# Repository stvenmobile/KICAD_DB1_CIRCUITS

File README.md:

# KICAD_DB1

This repository contains KICAD materials related to circuit boards used in the DB1 robot.

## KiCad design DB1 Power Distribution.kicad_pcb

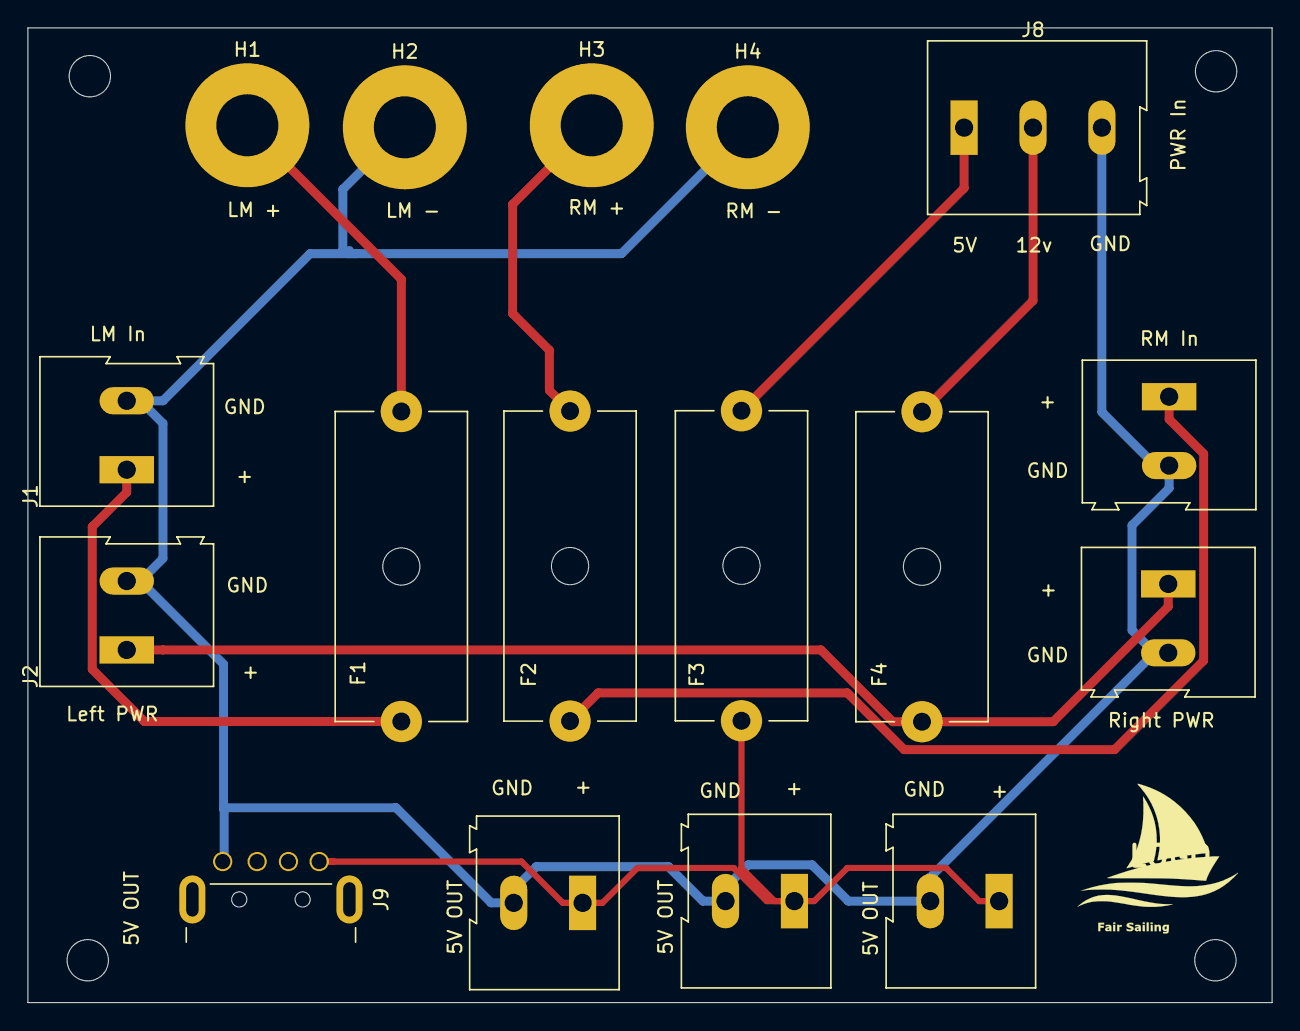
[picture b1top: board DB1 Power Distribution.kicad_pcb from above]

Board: 2 copper layers, 90.3 x 70.7 mm, 17 parts (0 on the bottom side), 9 nets.

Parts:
F1, F2, F3, F4: Fuse; Fuseholder_Cylinder-5x20mm_Schurter_0031_8201_Horizontal_Op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
H1: LM +; MountingHole_4.5mm_Pad
H2: LM -; MountingHole_4.5mm_Pad
H3: RM +; MountingHole_4.5mm_Pad
H4: RM -; MountingHole_4.5mm_Pad
J1: LM In; TerminalBlock_Altech_AK300-2_P5.00mm
J2: Left PWR; TerminalBlock_Altech_AK300-2_P5.00mm
J3: RM In; TerminalBlock_Altech_AK300-2_P5.00mm
J4: Right PWR; TerminalBlock_Altech_AK300-2_P5.00mm
J5, J6, J7: 5V Out; TerminalBlock_Altech_AK300-2_P5.00mm
J8: PWR In; TerminalBlock_Altech_AK300-3_P5.00mm
J9: USB_A; USB_A_CNCTech_1001-011-01101_Horizontal

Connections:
/5v: F3.2, J5.1, J6.1, J7.1, J9.1
/12v: F4.2, J2.1, J4.1
GND: H2.1, H4.1, J1.2, J2.2, J3.2, J4.2, J5.2, J6.2, J7.2, J8.3, J9.4
unnamed: F1.1, H1.1
unnamed: F1.2, J1.1
unnamed: F2.1, H3.1
unnamed: F2.2, J3.1
unnamed: F3.1, J8.1
unnamed: F4.1, J8.2
